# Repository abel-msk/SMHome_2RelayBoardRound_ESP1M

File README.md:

# SMHome 2RelayBoardRound ESP-01M — revision 8.2

**English** · [Русский](README.ru.md)

A round, two-layer Wi-Fi controller for roller shutters with two relay outputs, three wall-button inputs and two window reed-switch inputs. The controller is an **ESP-01M module with ESP8285 and 1 MB Flash**. Firmware is not included.

These images were rendered from the revision 8.2 PCB in KiCad, including the updated power-connector labels and mounting holes. Available footprint models are used; some packages are missing or represented by approximate models. The images are not a mechanical clearance check.

## Project files

Open `SMHome_2RelayBoardRound_ESP1M_v7.kicad_pro` in **KiCad 10**. Filenames retain the historical `_v7` suffix; `VERSION`, schematic/PCB title blocks and board revision silkscreen identify the current revision as **8.2**.

| File | Contents |
|---|---|
| `SMHome_2RelayBoardRound_ESP1M_v7.kicad_sch` | Root sheet: ESP module, relay drivers, indicators and programming connector |
| `PowerSupply.kicad_sch` | Mains protection, power conversion and power terminals |
| `ExtConnectors.kicad_sch` | Button/reed inputs, pull-ups, filters, protection and ADC selector |
| `SMHome_2RelayBoardRound_ESP1M_v7.kicad_pcb` | Two-layer PCB |

`MCU_STM32.kicad_sch` is a legacy file, not a sheet of the current ESP project. Existing Gerbers, plots, BOM exports and older images are historical outputs; regenerate manufacturing files from the current sources.

## How the circuit works

### Power supply

The mains supply enters through **J4**. **F1** protects the power-supply branch; **VR1 07D471K** is connected between the fused live rail and neutral. **DB1 MB8S** rectifies the input. **U2 BP2525F**, **L1 320 µH**, the switching diodes and capacitors form a non-isolated buck supply for **+5 V**. **R14 = 0.3 Ω** is the switching-current sense resistor. **C5 = 680 µF** provides output bulk capacitance.

**U4 AMS1117-3.3** supplies the ESP and input pull-ups from the +5 V rail. Its SOT-223 tab/pin 2 is connected to **+3V3**, not GND. The BP2525F DRAIN copper area is part of the high-voltage switching circuit.

**There is no galvanic isolation from the mains.** GND is connected to the rectifier negative rail. The 3.3 V and 5 V labels describe voltages relative to this GND; they do not identify a touch-safe supply. Do not connect GND to protective earth (PE). The enclosure, external switches, reed sensors, cables and connections must provide insulation suitable for the mains-related circuit. A small voltage across a contact does not make either conductor safe relative to earth.

### Relay outputs

**RL1/RL2 RJ-SS-105DM1** have 5 V coils and independent normally-open power contacts. **Q1/Q2 BC817** switch the coils through base resistors **R3/R7 = 1 kΩ**. **R1/R6 = 10 kΩ** pull the control signals down. **D1/D2** suppress coil turn-off transients; **D4/D5** indicate coil energization through **R4/R8 = 1 kΩ**.

Both contact circuits switch the live rail to separate motor-direction outputs. **The circuit has no hardware direction interlock**: both outputs can be energized together. A shutter installation needs a suitable interlock strategy. Firmware must also enforce mutually exclusive outputs, a motor-appropriate reversal delay and a movement timeout. Motor suitability requires checking the relay's inductive-load/inrush ratings; a resistive-load rating is insufficient.

### Buttons and window contacts

**SW1–SW3** are wall-button inputs; **SN1/SN2** are window reed-switch inputs. Each external dry contact closes its signal to **J2.7 / GND**. No external live voltage may be applied to J2.

All five channels have **4.7 kΩ pull-ups to +3V3** and **100 nF capacitors to GND**: open contact = HIGH, closed contact = LOW. The approximate closed-contact current is **0.7 mA**; switch contacts must be reliable at this small signal current.

| Input | GPIO / U1 pin | Pull-up | Series resistor | Capacitor | ESD diode |
|---|---|---|---|---|---|
| SW1 | GPIO10 / 12 | R17, 4.7 kΩ | R11, 100 Ω | C11, 100 nF | D10 |
| SW2 | GPIO16 / 17 | R18, 4.7 kΩ | R12, 100 Ω | C14, 100 nF | D11 |
| SW3 | GPIO4 / 10 | R16, 4.7 kΩ | None in the digital branch | C17, 100 nF | D9 |
| SN1 | GPIO14 / 15 | R20, 4.7 kΩ | R13, 100 Ω | C15, 100 nF | D12 |
| SN2 | GPIO13 / 5 | R21, 4.7 kΩ | R15, 100 Ω | C16, 100 nF | D13 |

**D9–D13 are PESD3V3L1BA** protection devices. R17/R18/R20/R21 connect on the connector side of the 100 Ω resistors; R16 connects directly to SW3, on the GPIO side of JP3. R26 belongs only to the ADC branch and does not serve as a series resistor for the SW3 button.

For approximately 2 m runs, use one twisted pair per input: **signal + circuit GND**. Cable insulation must suit the mains-related circuit; Ethernet category alone is not an insulation rating. Keep these cables away from motor/mains switching conductors. Add firmware debounce, for example 20–50 ms of stable input. Use plain input mode when external pull-ups are fitted. GPIO16 has no internal pull-up and should be polled rather than used with ESP8266 Arduino `attachInterrupt`.

For a window contact closed when the window is closed, an open window and a broken cable both produce HIGH. This is not a supervised loop and cannot distinguish those conditions.

### Assembly flags and mounting holes

The through-hole components **C2, C5, F1, J2, J3, J4, L1, R5, RL1, RL2 and VR1** are intended for **manual assembly**. DNP is disabled and they remain in the BOM; **Exclude from position files** is enabled in both schematic and PCB. They therefore remain visible on the schematic and in 3D while being omitted from pick-and-place output.

Former TP2–TP5 are now **H1–H4**, non-plated mounting holes with a **1.8 mm drill**. Their centres form a **32 × 32 mm square**, with horizontal and vertical sides, centred on the outer board outline. They have no electrical pins and are excluded from the BOM and placement files. The matching footprint is included in `Mechanical_Local.pretty`, referenced through `${KIPRJMOD}`.

## Connector pinouts

### J2 — buttons, reed switches and selectable ADC input

| Pin | Function |
|---:|---|
| 1 | SW3 or ADC, selected by JP3 |
| 2 | SW1 |
| 3 | SW2 |
| 4 | SN1 |
| 5 | SN2 |
| 6 | +3V3 |
| 7 | GND; common contact return, not PE |

### JP3 — digital/analog selection

- **1–2 closed:** J2.1 connects to SW3/GPIO4. R16 pulls this input up; the external button closes it to GND.
- **2–3 closed:** J2.1 feeds the ADC through R26. R16 and C17 remain on the disconnected GPIO4 branch.
- Do not bridge both positions at once.

```text
J2.1 ── JP3 2–3 ── R26 3 kΩ ──┬── ADC (U1.16)
                                │
                             R27 1 kΩ
                                │
                               GND
```

For a low-impedance voltage source, **Vadc = Vin / 4**. The divider presents approximately 4 kΩ input resistance: 3.3 V gives 0.825 V at the ADC; 3.6 V gives 0.900 V. With ±5% resistor tolerances, the worst-case ADC voltage at 3.6 V input is approximately 0.969 V. These are calculations, not measurements or simulation results. The ESP ADC range is 0–1 V. This input is not suitable for direct mains measurement or an unconditioned current-transformer output.

### J3 — programming and reset, 3.3 V logic

| Pin | Signal |
|---:|---|
| 1 | GND |
| 2 | +3V3 |
| 3 | ESP RX; connect adapter TX |
| 4 | ESP TX; connect adapter RX |
| 5 | Flash / GPIO0, U1.8 |
| 6 | NRST, U1.18; active LOW |

The former on-board reset and boot buttons are removed. To enter the bootloader, hold GPIO0 LOW while pulsing NRST LOW, then release reset and GPIO0. Use the numbered pinout above; the old nearby `3v3` silkscreen text has not been relocated for the expanded header.

**Disconnect all mains connections before programming** and supply the logic from an isolated 3.3 V source. Do not attach a conventional USB-UART adapter or an earth-referenced oscilloscope while mains power is present.

### J4 — mains and motor outputs

| Pin | Net | Function |
|---:|---|---|
| 1 | N | Motor neutral; directly connected to J4.2 |
| 2 | N | Mains neutral; directly connected to J4.1 |
| 3 | L | Mains live and relay contact supply |
| 4 | RL2 | Switched live through relay RL2 |
| 5 | RL1 | Switched live through relay RL1 |

**Revision 8.2 changes J4.1 from electronics GND to motor neutral N.** J4.1 and J4.2 are the same unswitched neutral net; J4 no longer exposes circuit GND. N is not GND or PE. The supply remains non-isolated, and the GND terminals on J2/J3 remain mains-related.

F1 protects only the board supply branch, not motor current through the relay contacts. Provide appropriate upstream motor/wiring protection separately.

### Relay GPIO mapping

| Function | GPIO | U1 pin |
|---|---:|---:|
| RL1 | 12 | 14 |
| RL2 | 5 | 13 |

GPIO2 and GPIO15 are not used for the external contacts. Firmware must use the revision 8 mapping, including GPIO16 for SW2, and a Flash configuration compatible with using GPIO10 on this module.

## Libraries and 3D models

The project uses standard KiCad libraries plus custom libraries referenced by `sym-lib-table` and `fp-lib-table`. These tables currently contain local absolute paths and need adjustment on another machine. Configure the custom symbols/footprints locally and set **`KIKAD_USER_3DMODELS`** (historical spelling) to the custom 3D-model directory. The ESP-01M STEP and STEP-derived WRL use matching offsets and the same custom-model variable; STEP is the visible model. Embedded symbols and board footprints preserve the current design, but cloning the repository does not install all editing libraries or models.

The PNG renders are included so the board can be viewed on GitHub without those libraries. Older `images/3dview.png` and `images/top.png` are not revision 8.2 illustrations.

## Revision 8.2 and verification status

Changes in 8.2:

- J4.1 changed from GND to motor neutral N, directly connected to mains neutral on J4.2.
- Power-connector silkscreen corrected on both sides; revision metadata and board marking updated to 8.2.
- ESP-01M model references corrected; new 3D renders and bilingual connector documentation.

Changes in 8.1:

- Through-hole components remain fitted and in the BOM, but are excluded from placement files for manual assembly.
- Mounting-hole centres aligned to a board-centred **32 × 32 mm square**; drill diameter remains **1.8 mm**, non-plated.
- Revision updated in project metadata and board silkscreen.

Changes inherited from revision 8:

- Updated component population and routing; five external 4.7 kΩ input pull-ups added.
- R26 moved exclusively into the ADC branch; R16 placed on SW3 so it does not bias ADC mode.
- Separate SW1 and selectable SW3/ADC terminals; J3 expanded to six programming/reset pins.
- On-board reset/boot buttons and the separate GPIO9 indicator removed; relay GPIO mapping updated.
- Revision 8 title blocks and board marking, bilingual documentation and new 3D renders.

Checks performed with KiCad 10.0.8 on **2026-11-18**, against the saved project:

| Check | Result |
|---|---|
| Schematic component inventory | 64 symbols, including connectors and four mechanical holes |
| DRC after zone refill | 0 errors, 55 warnings; 0 unconnected items |
| Schematic/PCB parity | 0 issues |
| ERC | 10 errors, 349 warnings |

The minimum thermal-spoke requirement is now 1 for the board; J2.7 has a local thermal gap of 0.25 mm. DRC warnings include 27 footprint-library mismatches, 21 silkscreen/edge clearances and 7 isolated copper areas. ERC includes unconnected pins, the unmatched `AC_SENS` hierarchical sheet pin, a pin-type conflict and power-input declarations; most warnings are off-grid endpoints and symbol-library mismatches. The `JP2` text beside J2.6 is a legacy label; that terminal is +3V3.

**Revision 8.2 is a saved development revision, not a fabrication-ready or safety-certified release.** Remaining electrical/layout issues, motor interlocking, external insulation and final mechanical fit require resolution/validation before manufacture or mains operation. No hardware measurements, new SPICE simulations or full compliance assessment were performed for this documentation update.

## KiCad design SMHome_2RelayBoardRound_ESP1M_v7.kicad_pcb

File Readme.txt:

Финальная версия платы с ESP-01M.   Вертикальная плата  с ESP-8266
Поправлено подключение РЕЛЕ 2 к новому пину.

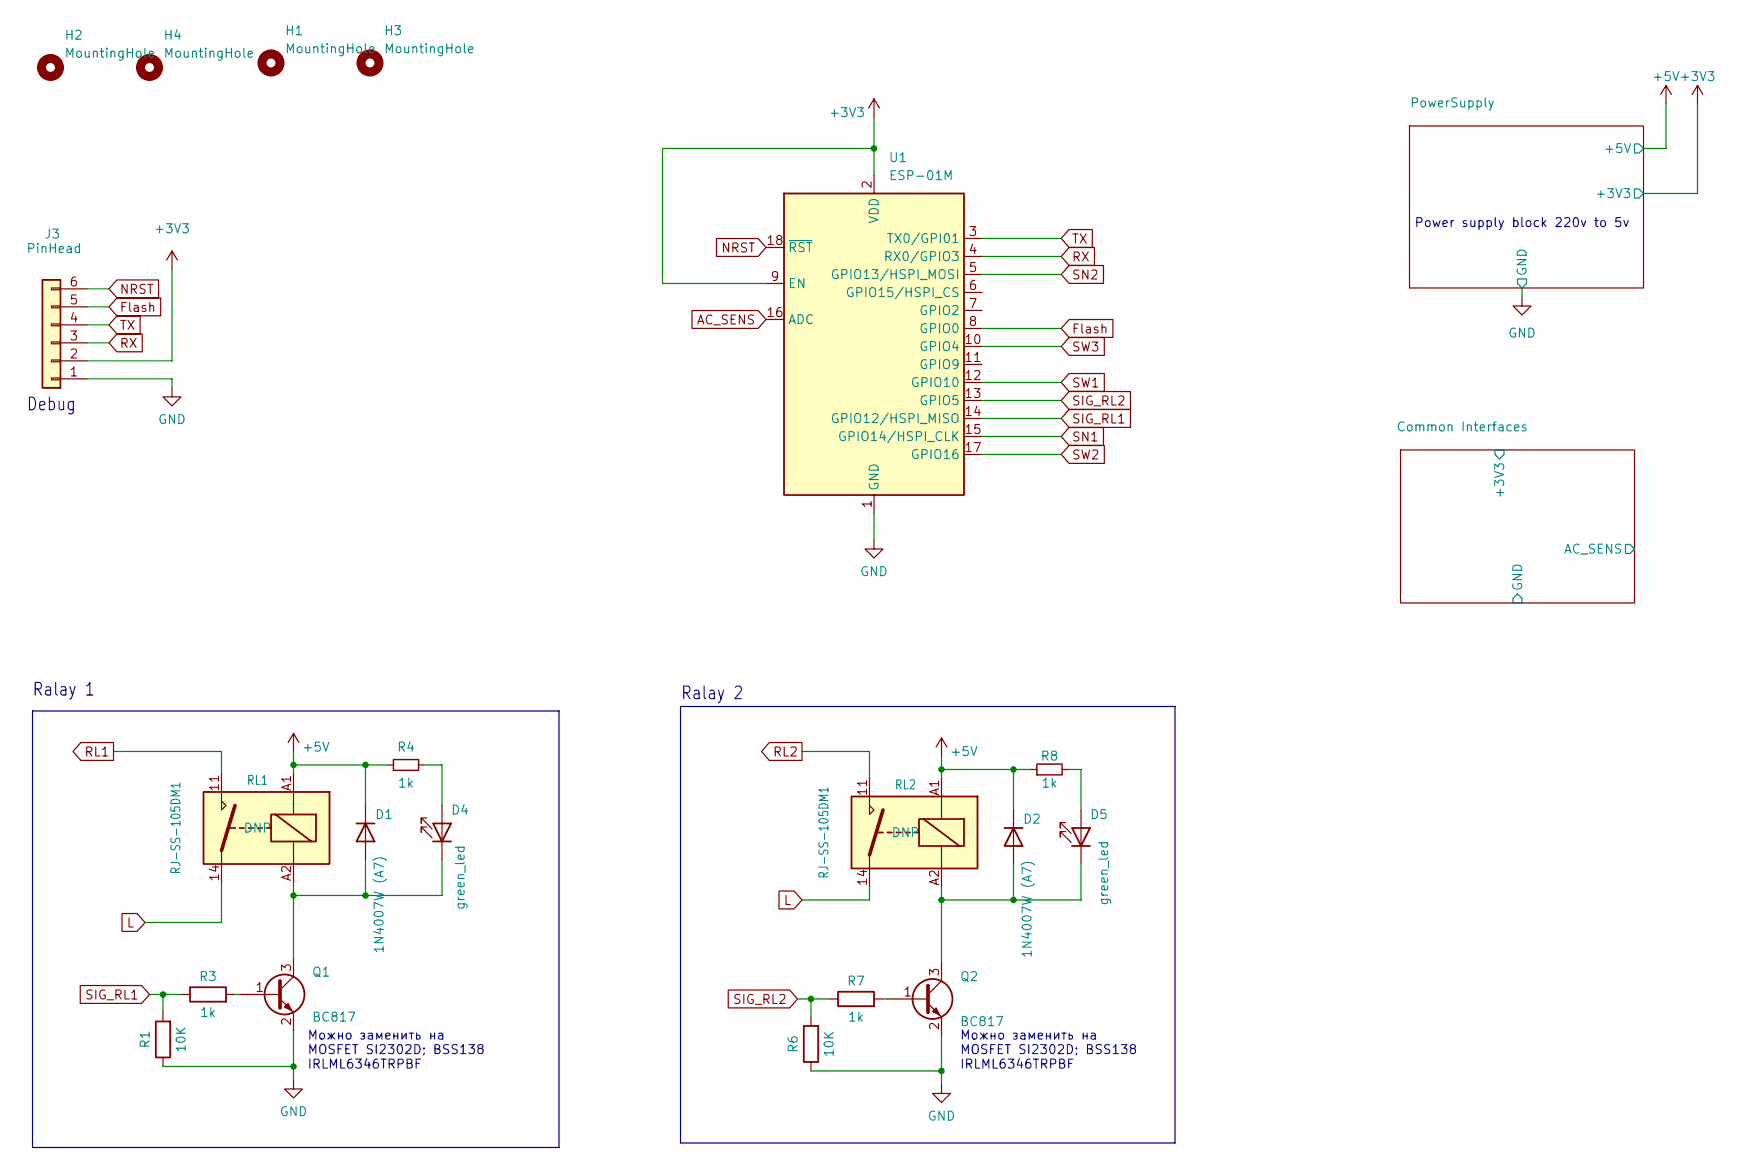
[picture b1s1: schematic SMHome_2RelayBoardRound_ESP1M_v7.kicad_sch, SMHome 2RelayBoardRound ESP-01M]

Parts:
D1, D2: 1N4007W (A7); D_SOD-123F
D4, D5: green_led; LED_0603_1608Metric_Pad1.05x0.95mm_HandSolder
H1, H2, H3, H4: MountingHole; MountingHole_1.8mm
J3: PinHead; PinHeader_1x06_P2.54mm_Vertical
Q1, Q2: BC817; SOT-23
R1, R6: 10K; R_0603_1608Metric_Pad0.98x0.95mm_HandSolder
R3, R4, R7, R8: 1k; R_0603_1608Metric_Pad0.98x0.95mm_HandSolder
RL1, RL2: RJ-SS-105DM1
U1: ESP-01M

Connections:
+3V3: J3.2, U1.2 (VDD), U1.9 (EN); also elsewhere on the board
+5V: D1.1 (K), D2.1 (K), R4.1, R8.1, RL1.A1, RL2.A1; also elsewhere on the board
AC_SENS: U1.16 (ADC); also elsewhere on the board
Flash: J3.5, U1.8 (GPIO0)
GND: J3.1, Q1.2 (E), Q2.2 (E), R1.1, R6.1, U1.1 (GND); also elsewhere on the board
L: RL1.14, RL2.14; also elsewhere on the board
NRST: J3.6, U1.18 (~RST)
unnamed: D1.2 (A), D4.1 (K), Q1.3 (C), RL1.A2
unnamed: D2.2 (A), D5.1 (K), Q2.3 (C), RL2.A2
unnamed: D4.2 (A), R4.2
unnamed: D5.2 (A), R8.2
unnamed: Q1.1 (B), R3.2
unnamed: Q2.1 (B), R7.2
RL1: RL1.11; also elsewhere on the board
RL2: RL2.11; also elsewhere on the board
RX: J3.3, U1.4 (RX0/GPIO3)
SIG_RL1: R1.2, R3.1, U1.14 (GPIO12/HSPI_MISO)
SIG_RL2: R6.2, R7.1, U1.13 (GPIO5)
SN1: U1.15 (GPIO14/HSPI_CLK); also elsewhere on the board
SN2: U1.5 (GPIO13/HSPI_MOSI); also elsewhere on the board
SW1: U1.12 (GPIO10); also elsewhere on the board
SW2: U1.17 (GPIO16); also elsewhere on the board
SW3: U1.10 (GPIO4); also elsewhere on the board
TX: J3.4, U1.3 (TX0/GPI01)

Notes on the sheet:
Power supply block 220v to 5v
Можно заменить на MOSFET SI2302D; BSS138 IRLML6346TRPBF
Debug
Ralay 2
Ralay 1

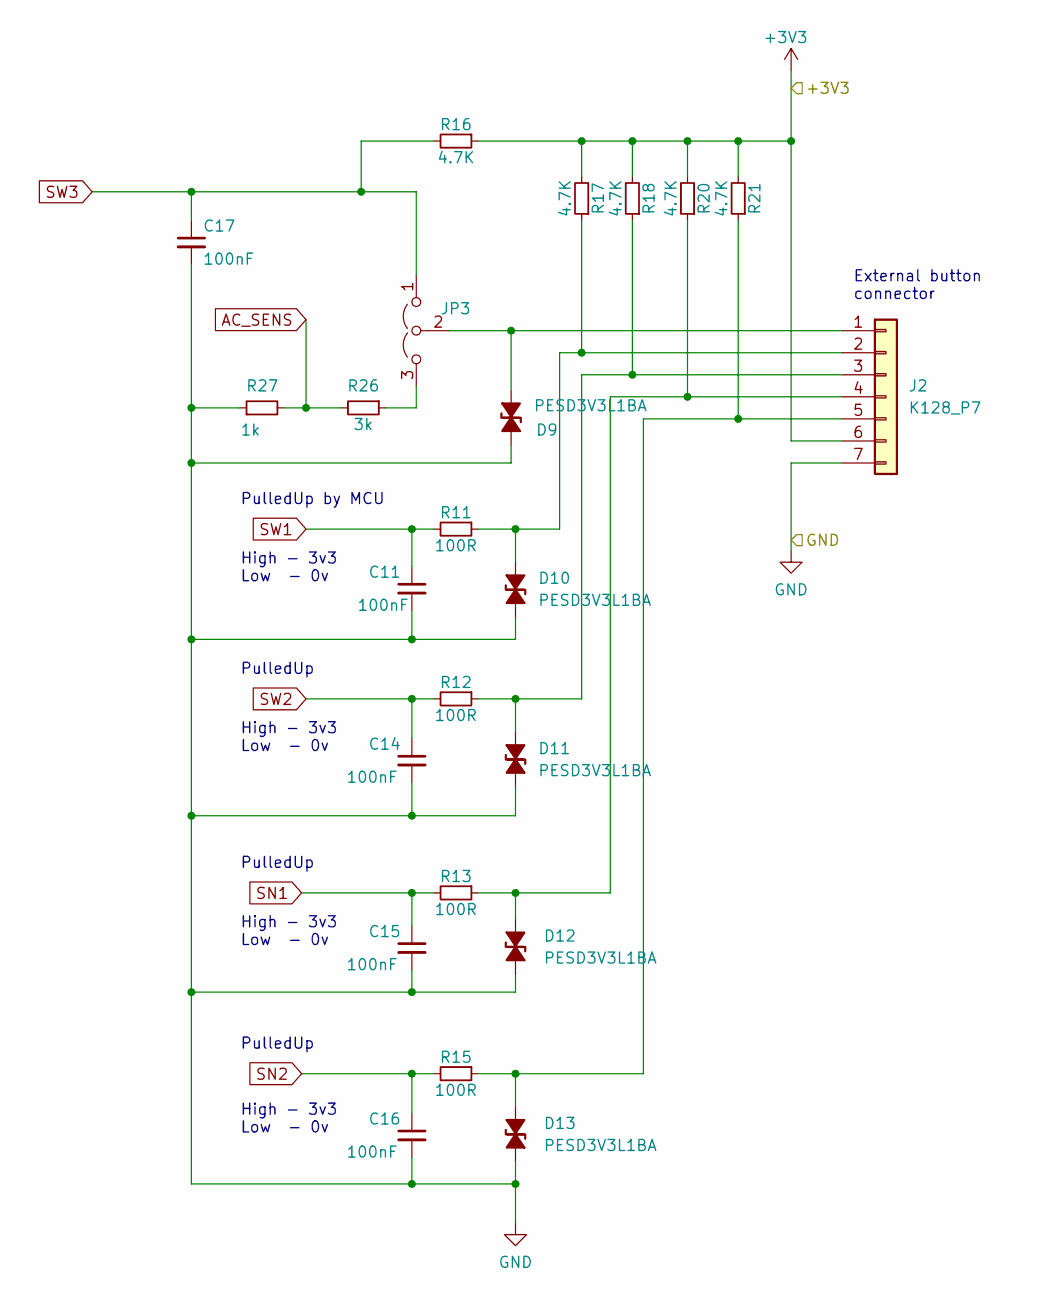
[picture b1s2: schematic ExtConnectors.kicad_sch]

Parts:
C11, C14, C15, C16, C17: 100nF; C_0805_2012Metric
D9, D10, D11, D12, D13: PESD3V3L1BA; D_SOD-323_HandSoldering
J2: K128_P7; Phoenix Contact_MPT-0,5_7_2,54_P7
JP3: jmp3; SolderJumper-3_P1.3mm_Open_RoundedPad1.0x1.5mm_NumberLabels
R11, R12, R13, R15: 100R; R_0805_2012Metric
R16, R17, R18, R20, R21: 4.7К; R_0805_2012Metric
R26: 3k; R_0805_2012Metric
R27: 1k; R_0603_1608Metric_Pad0.98x0.95mm_HandSolder

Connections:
+3V3: J2.6, R16.1, R17.2, R18.2, R20.2, R21.2; also elsewhere on the board
AC_SENS: R26.2, R27.2; also elsewhere on the board
GND: C11.2, C14.2, C15.2, C16.2, C17.2, D9.2 (A), D10.2 (A), D11.2 (A), D12.2 (A), D13.2 (A), J2.7, R27.1; also elsewhere on the board
unnamed: D9.1 (K), J2.1, JP3.2 (C)
unnamed: D10.1 (K), J2.2, R11.1, R17.1
unnamed: D11.1 (K), J2.3, R12.1, R18.1
unnamed: D12.1 (K), J2.4, R13.1, R20.1
unnamed: D13.1 (K), J2.5, R15.1, R21.1
unnamed: JP3.3 (B), R26.1
SN1: C15.1, R13.2; also elsewhere on the board
SN2: C16.1, R15.2; also elsewhere on the board
SW1: C11.1, R11.2; also elsewhere on the board
SW2: C14.1, R12.2; also elsewhere on the board
SW3: C17.1, JP3.1 (A), R16.2; also elsewhere on the board

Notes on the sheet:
External button connector
PulledUp
High - 3v3 Low - 0v
PulledUp by MCU

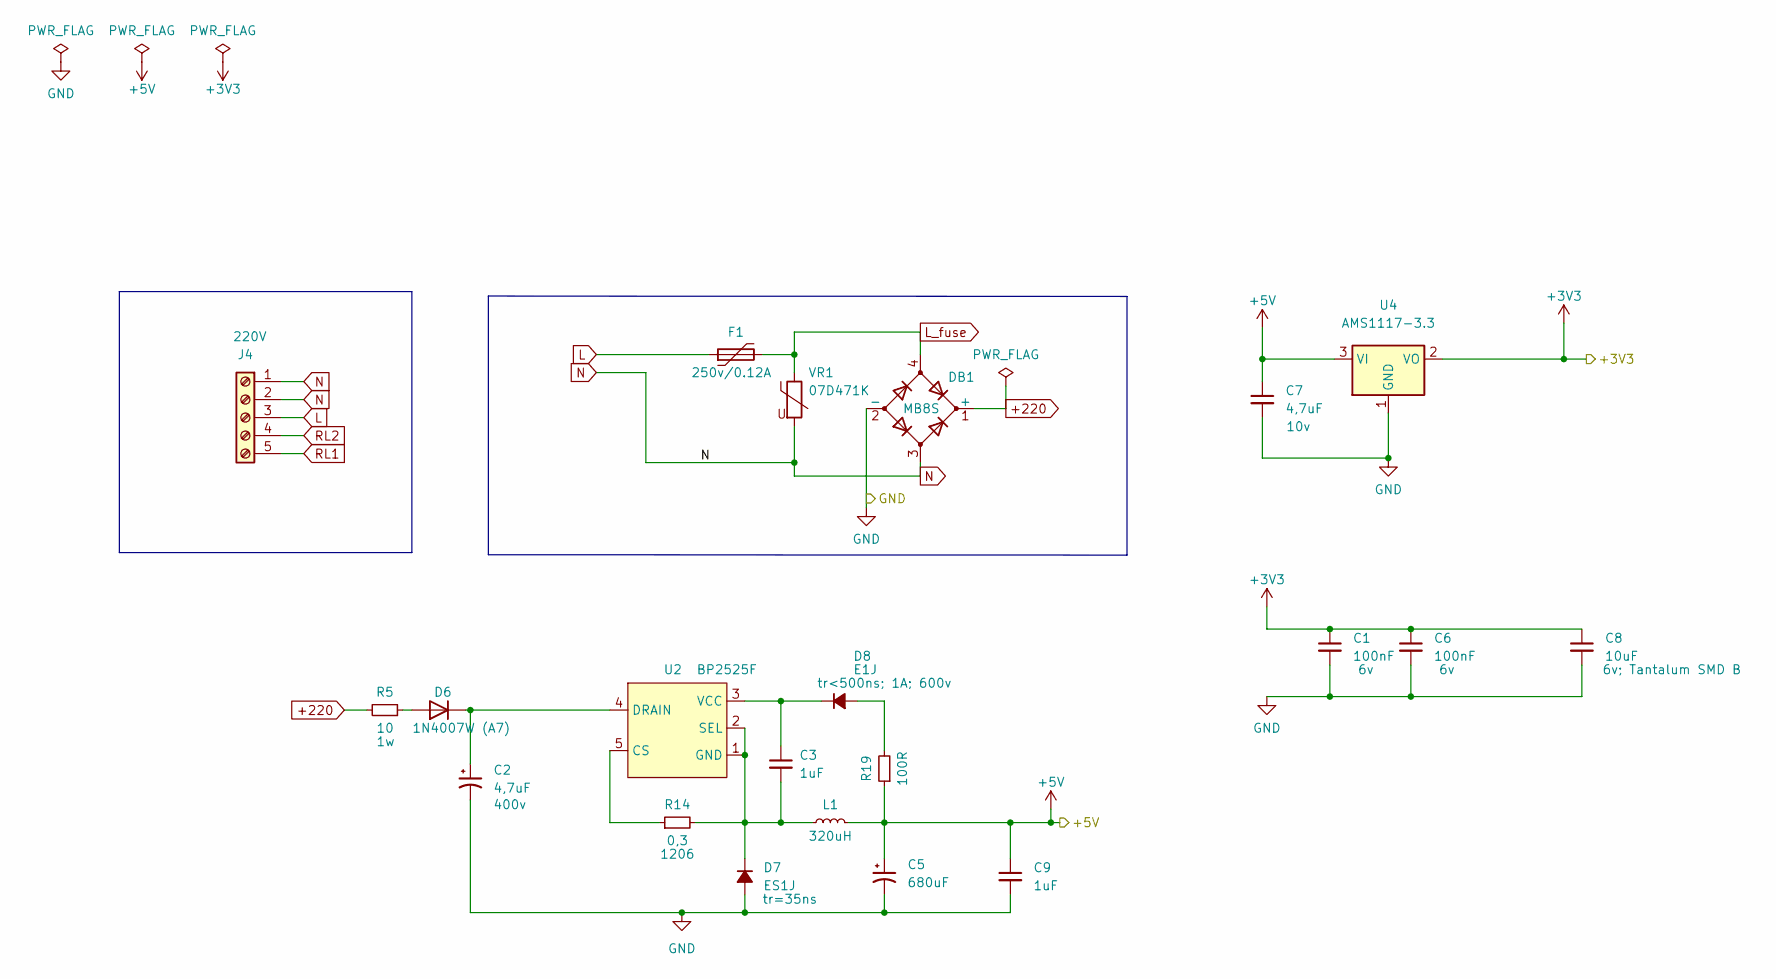
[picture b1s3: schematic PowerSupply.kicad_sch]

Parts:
C1, C6: 100nF; C_0805_2012Metric
C2: 4,7uF; CP_Radial_D8.0mm_P3.80mm
C3, C9: 1uF; C_0805_2012Metric_Pad1.18x1.45mm_HandSolder
C5: 680uF; CP_Radial_D6.3mm_P2.50mm
C7: 4,7uF; C_0805_2012Metric_Pad1.18x1.45mm_HandSolder
C8: 10uF; CP_EIA-3528-21_Kemet-B
D6: 1N4007W (A7); D_SOD-123F
D7: ES1J; D_SMA
D8: E1J; D_SOD-123F
DB1: MB8S; MBS
F1: 250v/0.12A; RF145_D6.5mm_W4mm
J4: 220V; DG301-5.0-05P
L1: 320uH; L_Radial_D10.0mm_P5.00mm_Fastron_07P
R5: 10; R_Axial_DIN0414_L11.9mm_D4.5mm_P5.08mm_Vertical
R14: 0,3; R_1206_3216Metric_Pad1.30x1.75mm_HandSolder
R19: 100R; R_0603_1608Metric_Pad0.98x0.95mm_HandSolder
U2: BP2525F; SOT33-5
U4: AMS1117-3.3; SOT-223-3_TabPin2
VR1: 07D471K; RV_Disc_D9mm_W3.3mm_P5mm

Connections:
+3V3: C1.1, C6.1, C8.1, U4.2 (VO); also elsewhere on the board
+5V: C5.1, C7.1, C9.1, L1.2, R19.1, U4.3 (VI); also elsewhere on the board
+220: DB1.1 (+), R5.2
GND: C1.2, C2.2, C5.2, C6.2, C7.2, C8.2, C9.2, D7.2 (A), DB1.2 (-), U4.1 (GND); also elsewhere on the board
L: F1.1, J4.3; also elsewhere on the board
L_fuse: DB1.4, F1.2, VR1.1
N: DB1.3, J4.1, J4.2, VR1.2
unnamed: D6.2 (A), R5.1
unnamed: C2.1, D6.1 (K), U2.4 (DRAIN)
unnamed: C3.2, D7.1 (K), L1.1, R14.2, U2.1 (GND), U2.2 (SEL)
unnamed: D8.2 (A), R19.2
unnamed: C3.1, D8.1 (K), U2.3 (VCC)
unnamed: R14.1, U2.5 (CS)
RL1: J4.5; also elsewhere on the board
RL2: J4.4; also elsewhere on the board

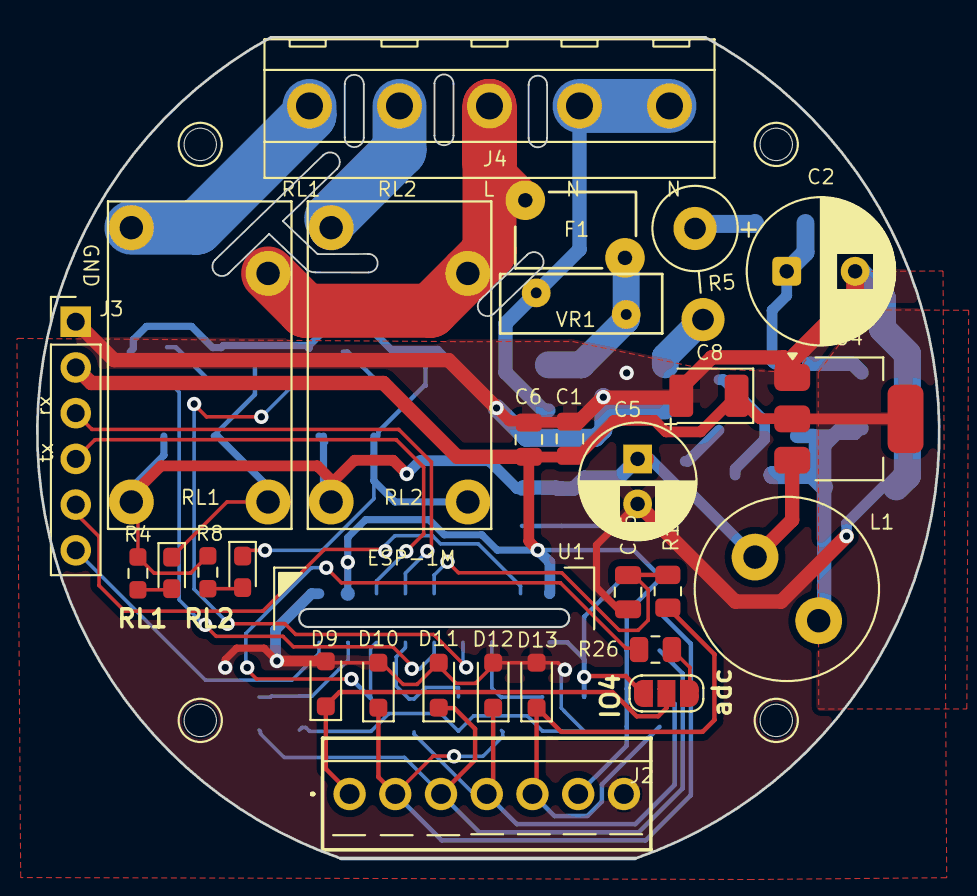
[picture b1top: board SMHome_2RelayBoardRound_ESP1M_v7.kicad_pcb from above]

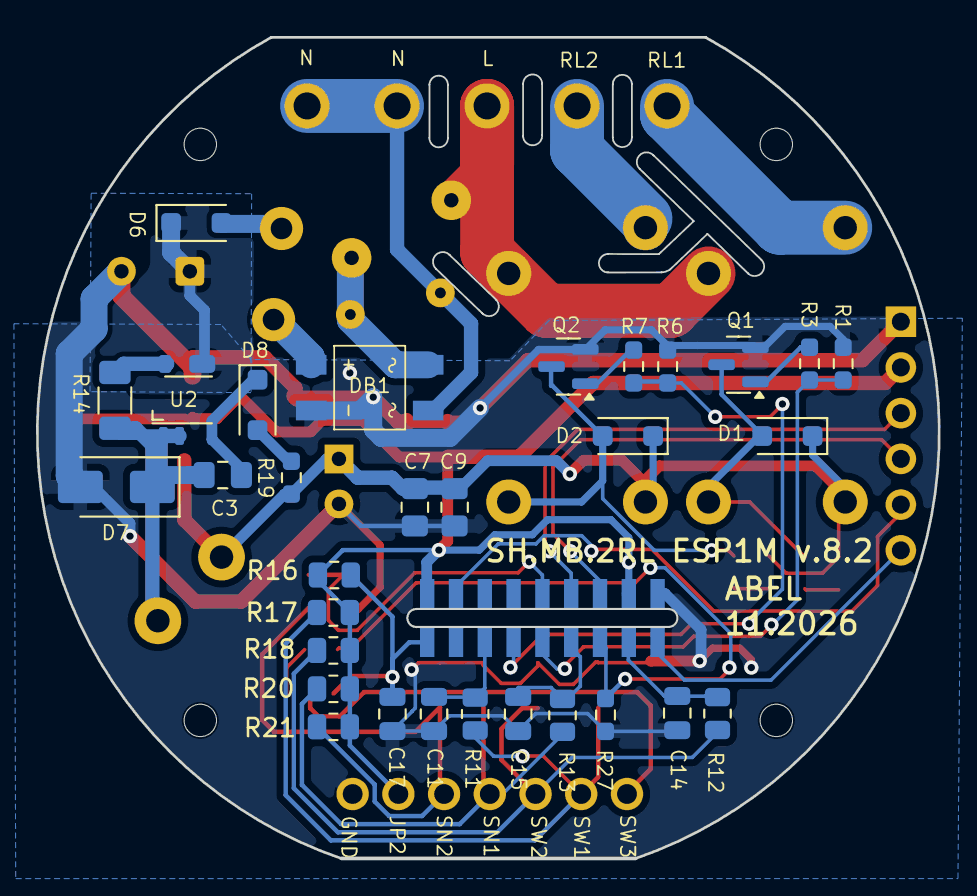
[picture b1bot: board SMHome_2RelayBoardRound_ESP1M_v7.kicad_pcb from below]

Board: 2 copper layers, 50.1 x 45.6 mm, 64 parts (31 on the bottom side), 39 nets.

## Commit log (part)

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2025-02-24 add gitignore
2025-11-26 Migrated to KiKad9
